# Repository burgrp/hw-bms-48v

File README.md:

# hw-bms-48v
48V/200A battery monitoring system

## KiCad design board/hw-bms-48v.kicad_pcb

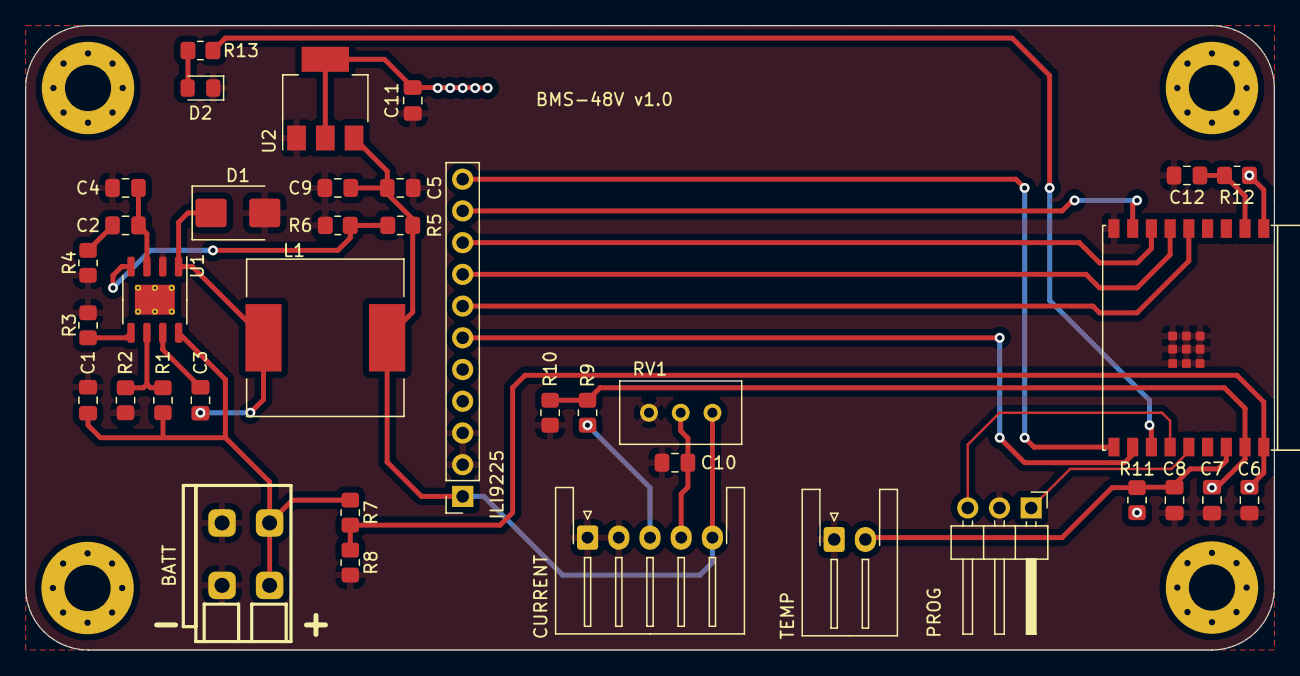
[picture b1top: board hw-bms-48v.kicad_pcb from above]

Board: 2 copper layers, 100.0 x 50.0 mm, 41 parts (0 on the bottom side), 27 nets.

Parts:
C1: 10u/100V; C_0805_2012Metric_Pad1.18x1.45mm_HandSolder
C2: 6n8; C_0805_2012Metric_Pad1.18x1.45mm_HandSolder
C3: 100n; C_0805_2012Metric_Pad1.18x1.45mm_HandSolder
C4: ???; C_0805_2012Metric_Pad1.18x1.45mm_HandSolder
C5, C9, C11: 47u; C_0805_2012Metric_Pad1.18x1.45mm_HandSolder
C6, C7, C8, C10, C12: 1u; C_0805_2012Metric_Pad1.18x1.45mm_HandSolder
D1: SK22; D_SMB
D2: LED; LED_0805_2012Metric_Pad1.15x1.40mm_HandSolder
H1, H2, H3, H4: MountingHole; MountingHole_3.7mm_Pad_Via
J1: BATT; DG235-3.81-02P
J2: PROG; PinHeader_1x03_P2.54mm_Horizontal
J3: CURRENT; JST_XH_S5B-XH-A-1_1x05_P2.50mm_Horizontal
J4: TEMP; JST_XH_S2B-XH-A-1_1x02_P2.50mm_Horizontal
J5: ILI9225; PinSocket_1x11_P2.54mm_Vertical
L1: 33uH; L_12x12mm_H6mm
R1, R7, R10: 100k; R_0805_2012Metric_Pad1.20x1.40mm_HandSolder
R2: 20k; R_0805_2012Metric_Pad1.20x1.40mm_HandSolder
R3: 47k; R_0805_2012Metric_Pad1.20x1.40mm_HandSolder
R4, R12: 10k; R_0805_2012Metric_Pad1.20x1.40mm_HandSolder
R5: 3k; R_0805_2012Metric_Pad1.20x1.40mm_HandSolder
R6: 750R; R_0805_2012Metric_Pad1.20x1.40mm_HandSolder
R8: 3k9; R_0805_2012Metric_Pad1.20x1.40mm_HandSolder
R9, R11: 27k; R_0805_2012Metric_Pad1.20x1.40mm_HandSolder
R13: 270R; R_0805_2012Metric_Pad1.20x1.40mm_HandSolder
RV1: 10k; Potentiometer_Bourns_3296W_Vertical
U1: BD9G341EFJ; HTSOP-8-1EP_3.9x4.9mm_P1.27mm_EP2.4x3.2mm_ThermalVias
U2: LM1117MP-3.3; SOT-223-3_TabPin2
U3: ESP32-C3-WROOM-02

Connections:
+3V3: C11.2, R11.1, R12.1, U2.2 (VO), U3.1 (3V3)
+5V: C5.2, C9.2, J3.5, J5.1, L1.2, R5.1, RV1.3, U2.3 (VI)
+BATT: C1.2, J1.2, R1.1, R7.1, U1.8 (VCC)
/LCD_BL: J5.6, U3.11 (GPIO20/U0RXD)
/LCD_RS: J5.9, U3.7 (GPIO8)
/LCD_RST: J5.10, U3.8 (GPIO9)
/LCD_SCK: J5.7, U3.5 (GPIO6)
/LCD_SDI: J5.8, U3.6 (GPIO7)
/LCD_SS: J5.11, U3.10 (GPIO10)
/LED: R13.1, U3.12 (GPIO21/U0TXD)
/USB_D+: J2.1, U3.14 (GPIO19/USB_D+)
/USB_D-: J2.3, U3.13 (GPIO18/USB_D-)
GND: C1.1, C4.1, C5.1, C6.1, C7.1, C8.1, C9.1, C10.1, C11.1, C12.1, D1.2 (A), D2.1 (K), J1.1, J2.2, J3.1, J3.2, J4.1, J5.2, J5.3, R2.2, R3.2, R4.2, R6.2, R8.2, R10.2, RV1.1, U1.2 (GND), U2.1 (GND), U3.9 (GND), U3.19 (GND)
unnamed: C2.1, R4.1
unnamed: C3.1, D1.1 (K), L1.1, U1.1 (LX)
unnamed: D2.2 (A), R13.2
unnamed: J3.3, R9.1
unnamed: C10.2, J3.4, RV1.2
unnamed: C8.2, J4.2, R11.2, U3.16 (GPIO2/ADC1_CH2)
unnamed: C3.2, U1.7 (BST)
unnamed: R1.2, R2.1, U1.6 (EN)
unnamed: R5.2, R6.1, U1.4 (FB)
unnamed: R3.1, U1.5 (RT)
unnamed: C2.2, C4.2, U1.3 (VC)
unnamed: C12.2, R12.2, U3.2 (EN/CHIP_PU)
unnamed: C6.2, R7.2, R8.1, U3.18 (GPIO0/ADC1_CH0/XTAL_32K_P)
unnamed: C7.2, R9.2, R10.1, U3.17 (GPIO1/ADC1_CH1/XTAL_32K_N)

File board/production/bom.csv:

Designator,Footprint,Quantity,Value,LCSC Part #
C1,0805,1,10u/100V,
C10,0805,1,1u,
C11,0805,1,47u,
C12,0805,1,1u,
C2,0805,1,6n8,
C3,0805,1,100n,
C4,0805,1,???,
C5,0805,1,47u,
C6,0805,1,1u,
C7,0805,1,1u,
C8,0805,1,1u,
C9,0805,1,47u,
D1,D_SMB,1,SK22,
D2,0805,1,LED,
"H1, H2, H3, H4",MountingHole_3.7mm_Pad_Via,4,MountingHole,
J1,DG235-3.81-02P,1,BATT,
J2,PinHeader_1x03_P2.54mm_Horizontal,1,PROG,
J3,JST_XH_S5B-XH-A-1_1x05_P2.50mm_Horizontal,1,CURRENT,
J4,JST_XH_S2B-XH-A-1_1x02_P2.50mm_Horizontal,1,TEMP,
J5,PinSocket_1x11_P2.54mm_Vertical,1,ILI9225,
L1,L_12x12mm_H6mm,1,33uH,
R1,0805,1,100k,
R10,0805,1,100k,
R11,0805,1,27k,
R12,0805,1,10k,
R13,0805,1,270R,
R2,0805,1,20k,
R3,0805,1,47k,
R4,0805,1,10k,
R5,0805,1,3k,
R6,0805,1,750R,
R7,0805,1,100k,
R8,0805,1,3k9,
R9,0805,1,27k,
RV1,Potentiometer_Bourns_3296W_Vertical,1,10k,
U1,HTSOP-8-1EP_3.9x4.9mm_P1.27mm_EP2.4x3.2mm_ThermalVias,1,BD9G341EFJ,
U2,SOT-223-3_TabPin2,1,LM1117MP-3.3,
U3,ESP32-C3-WROOM-02,1,ESP32-C3-WROOM-02,
